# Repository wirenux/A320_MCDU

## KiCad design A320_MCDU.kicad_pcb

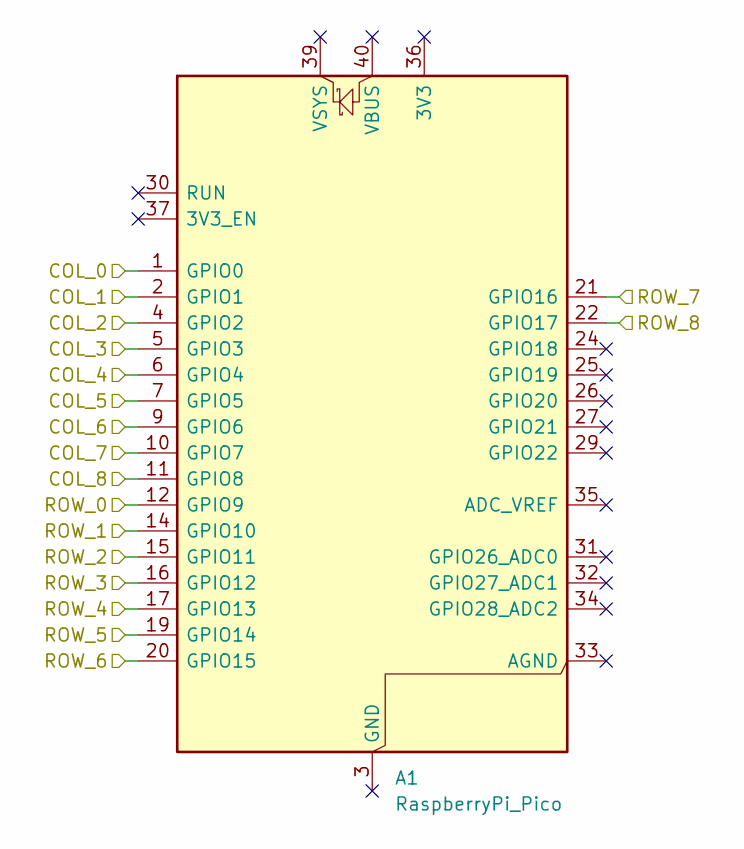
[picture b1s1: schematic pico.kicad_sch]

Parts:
A1: RaspberryPi_Pico; RaspberryPi_Pico_Common_Unspecified

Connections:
/Lower Pad/COL_3: A1.5 (GPIO3); also elsewhere on the board
/Lower Pad/COL_4: A1.6 (GPIO4); also elsewhere on the board
/Lower Pad/COL_5: A1.7 (GPIO5); also elsewhere on the board
/Lower Pad/COL_6: A1.9 (GPIO6); also elsewhere on the board
/Lower Pad/COL_7: A1.10 (GPIO7); also elsewhere on the board
/Lower Pad/ROW_5: A1.19 (GPIO14); also elsewhere on the board
/Lower Pad/ROW_6: A1.20 (GPIO15); also elsewhere on the board
/Lower Pad/ROW_7: A1.21 (GPIO16); also elsewhere on the board
/NumPad/COL_0: A1.1 (GPIO0); also elsewhere on the board
/NumPad/COL_1: A1.2 (GPIO1); also elsewhere on the board
/NumPad/COL_2: A1.4 (GPIO2); also elsewhere on the board
/NumPad/ROW_8: A1.22 (GPIO17); also elsewhere on the board
/Pico/COL_8: A1.11 (GPIO8); also elsewhere on the board
/Pico/ROW_0: A1.12 (GPIO9); also elsewhere on the board
/Pico/ROW_1: A1.14 (GPIO10); also elsewhere on the board
/Pico/ROW_2: A1.15 (GPIO11); also elsewhere on the board
/Pico/ROW_3: A1.16 (GPIO12); also elsewhere on the board
/Pico/ROW_4: A1.17 (GPIO13); also elsewhere on the board

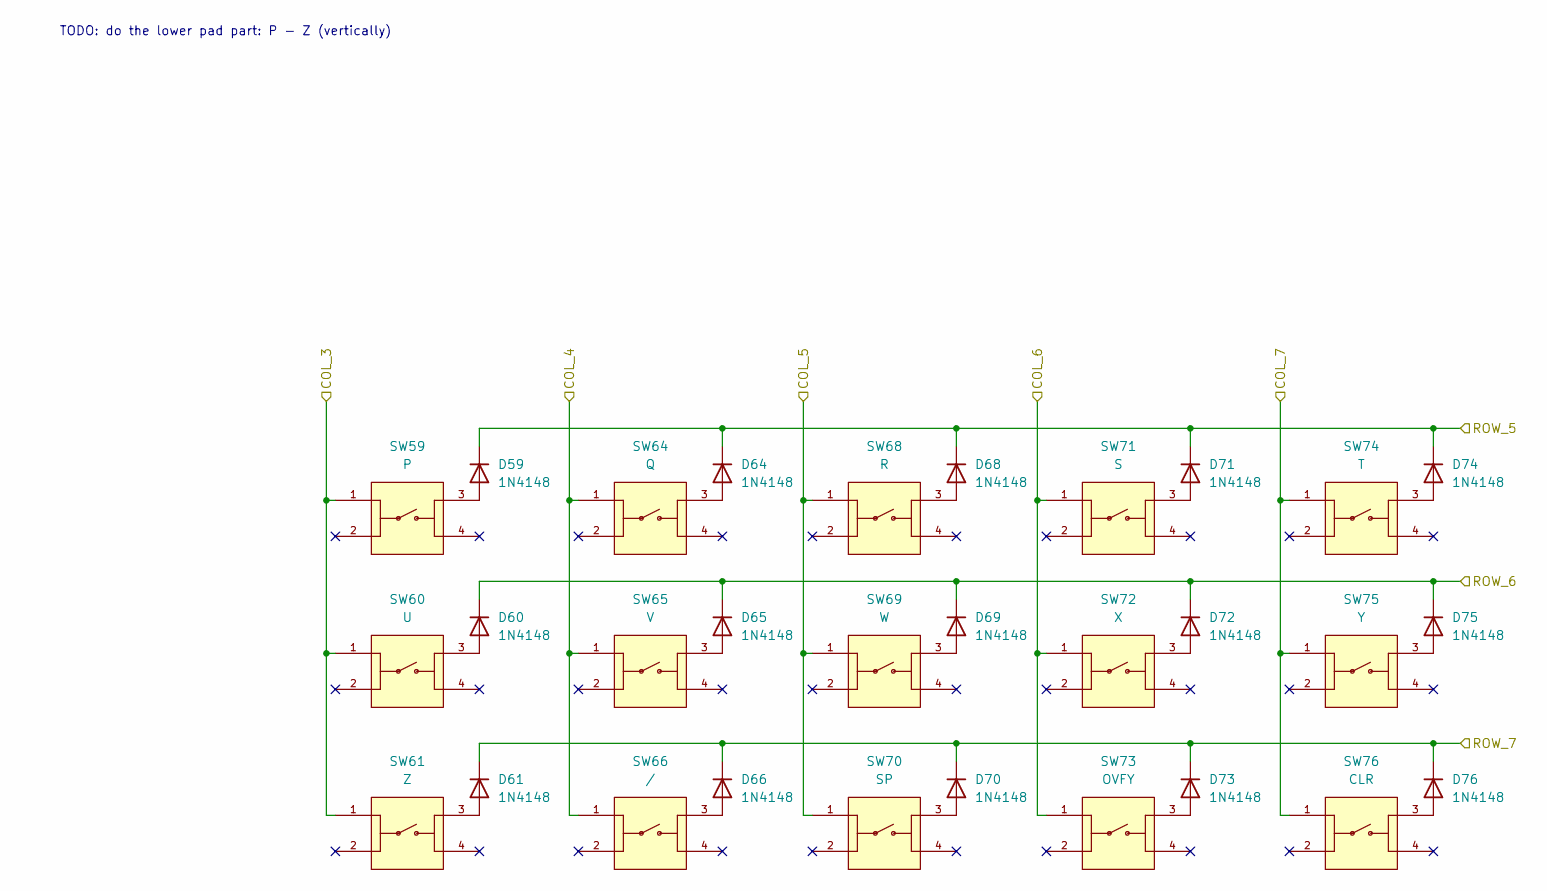
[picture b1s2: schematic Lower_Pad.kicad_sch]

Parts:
D59, D60, D61, D64, D65, D66, D68, D69, D70, D71, D72, D73, D74, D75, D76: 1N4148; D_DO-35_SOD27_P7.62mm_Horizontal
SW59: P; SW_1825910-6-4; PARTREV C10
SW60: U; SW_1825910-6-4; PARTREV C10
SW61: Z; SW_1825910-6-4; PARTREV C10
SW64: Q; SW_1825910-6-4; PARTREV C10
SW65: V; SW_1825910-6-4; PARTREV C10
SW66: /; SW_1825910-6-4; PARTREV C10
SW68: R; SW_1825910-6-4; PARTREV C10
SW69: W; SW_1825910-6-4; PARTREV C10
SW70: SP; SW_1825910-6-4; PARTREV C10
SW71: S; SW_1825910-6-4; PARTREV C10
SW72: X; SW_1825910-6-4; PARTREV C10
SW73: OVFY; SW_1825910-6-4; PARTREV C10
SW74: T; SW_1825910-6-4; PARTREV C10
SW75: Y; SW_1825910-6-4; PARTREV C10
SW76: CLR; SW_1825910-6-4; PARTREV C10

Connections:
/Lower Pad/COL_3: SW59.1, SW60.1, SW61.1; also elsewhere on the board
/Lower Pad/COL_4: SW64.1, SW65.1, SW66.1; also elsewhere on the board
/Lower Pad/COL_5: SW68.1, SW69.1, SW70.1; also elsewhere on the board
/Lower Pad/COL_6: SW71.1, SW72.1, SW73.1; also elsewhere on the board
/Lower Pad/COL_7: SW74.1, SW75.1, SW76.1; also elsewhere on the board
/Lower Pad/ROW_5: D59.1 (K), D64.1 (K), D68.1 (K), D71.1 (K), D74.1 (K); also elsewhere on the board
/Lower Pad/ROW_6: D60.1 (K), D65.1 (K), D69.1 (K), D72.1 (K), D75.1 (K); also elsewhere on the board
/Lower Pad/ROW_7: D61.1 (K), D66.1 (K), D70.1 (K), D73.1 (K), D76.1 (K); also elsewhere on the board
unnamed: D59.2 (A), SW59.3
unnamed: D60.2 (A), SW60.3
unnamed: D61.2 (A), SW61.3
unnamed: D64.2 (A), SW64.3
unnamed: D65.2 (A), SW65.3
unnamed: D66.2 (A), SW66.3
unnamed: D68.2 (A), SW68.3
unnamed: D69.2 (A), SW69.3
unnamed: D70.2 (A), SW70.3
unnamed: D71.2 (A), SW71.3
unnamed: D72.2 (A), SW72.3
unnamed: D73.2 (A), SW73.3
unnamed: D74.2 (A), SW74.3
unnamed: D75.2 (A), SW75.3
unnamed: D76.2 (A), SW76.3

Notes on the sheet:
TODO: do the lower pad part: P - Z (vertically)

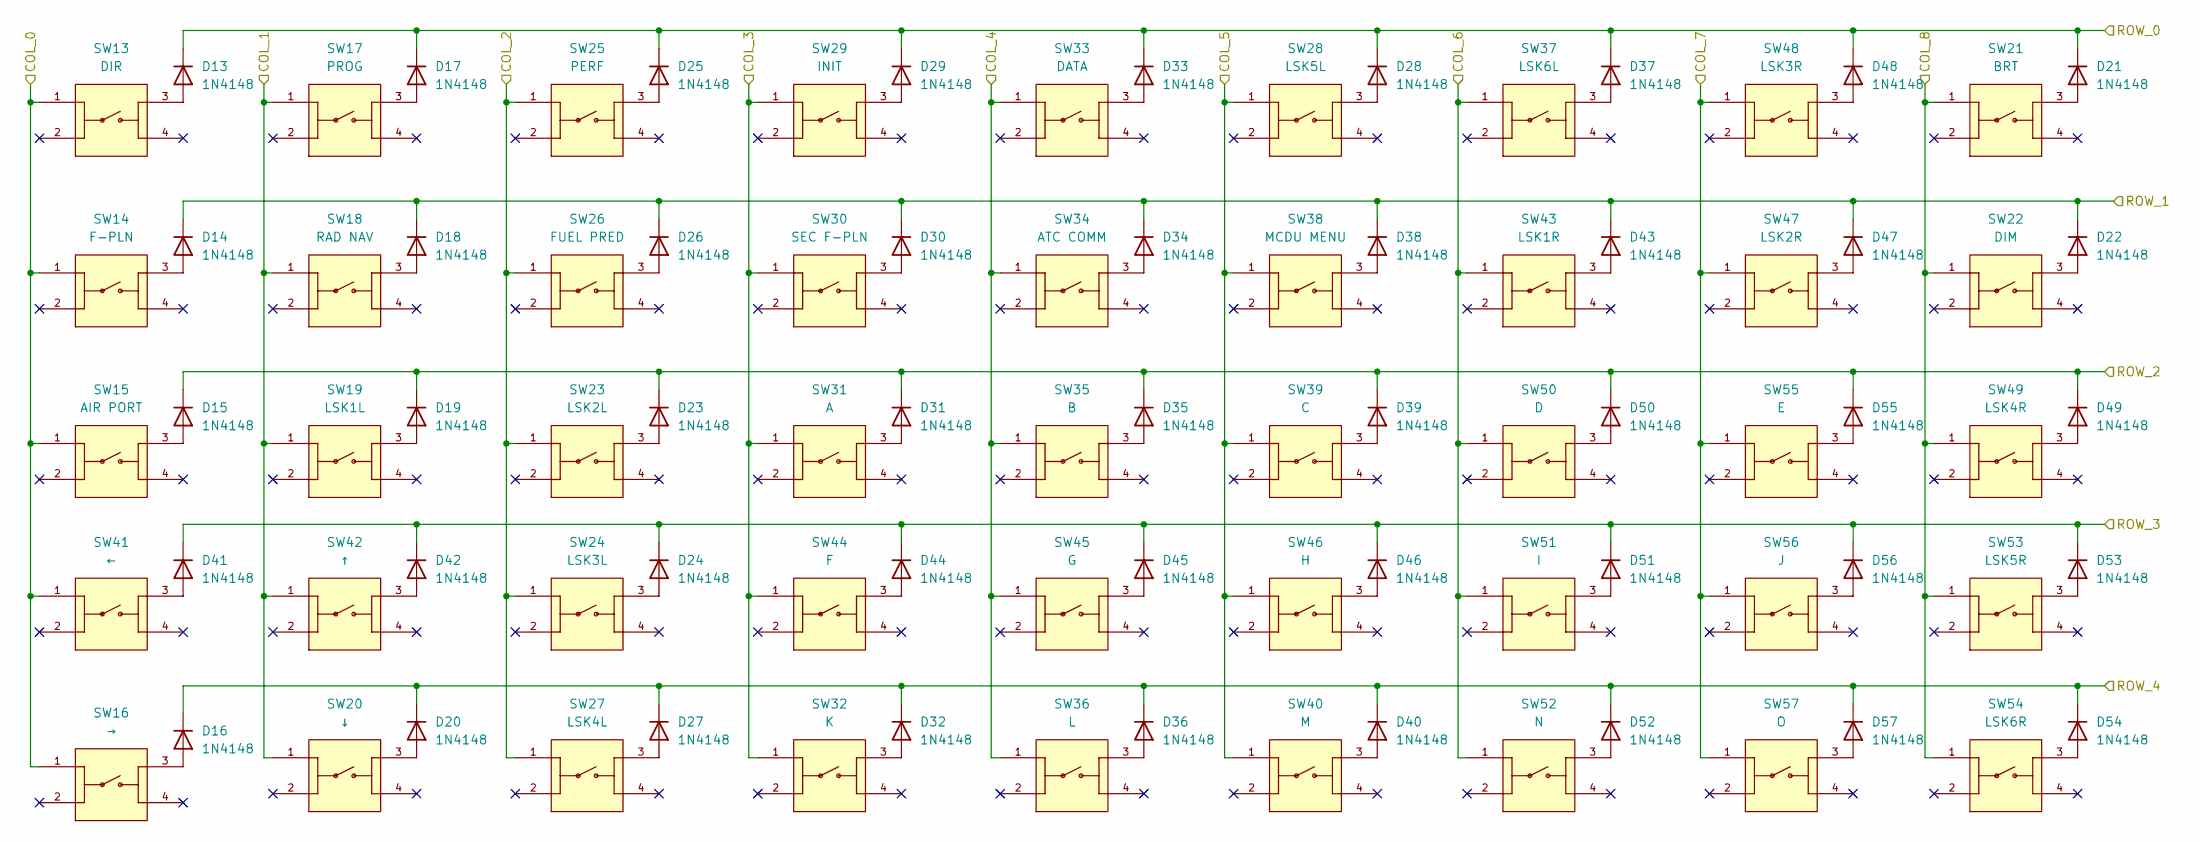
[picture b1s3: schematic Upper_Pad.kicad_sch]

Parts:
D13, D14, D15, D16, D17, D18, D19, D20, D21, D22, D23, D24, D25, D26, D27, D28, D29, D30, D31, D32, D33, D34, D35, D36, D37, D38, D39, D40, D41, D42, D43, D44, D45, D46, D47, D48, D49, D50, D51, D52, D53, D54, D55, D56, D57: 1N4148; D_DO-35_SOD27_P7.62mm_Horizontal
SW13: DIR; SW_1825910-6-4; PARTREV C10
SW14: F-PLN; SW_1825910-6-4; PARTREV C10
SW15: AIR PORT; SW_1825910-6-4; PARTREV C10
SW16: →; SW_1825910-6-4; PARTREV C10
SW17: PROG; SW_1825910-6-4; PARTREV C10
SW18: RAD NAV; SW_1825910-6-4; PARTREV C10
SW19: LSK1L; SW_1825910-6-4; PARTREV C10
SW20: ↓; SW_1825910-6-4; PARTREV C10
SW21: BRT; SW_1825910-6-4; PARTREV C10
SW22: DIM; SW_1825910-6-4; PARTREV C10
SW23: LSK2L; SW_1825910-6-4; PARTREV C10
SW24: LSK3L; SW_1825910-6-4; PARTREV C10
SW25: PERF; SW_1825910-6-4; PARTREV C10
SW26: FUEL PRED; SW_1825910-6-4; PARTREV C10
SW27: LSK4L; SW_1825910-6-4; PARTREV C10
SW28: LSK5L; SW_1825910-6-4; PARTREV C10
SW29: INIT; SW_1825910-6-4; PARTREV C10
SW30: SEC F-PLN; SW_1825910-6-4; PARTREV C10
SW31: A; SW_1825910-6-4; PARTREV C10
SW32: K; SW_1825910-6-4; PARTREV C10
SW33: DATA; SW_1825910-6-4; PARTREV C10
SW34: ATC COMM; SW_1825910-6-4; PARTREV C10
SW35: B; SW_1825910-6-4; PARTREV C10
SW36: L; SW_1825910-6-4; PARTREV C10
SW37: LSK6L; SW_1825910-6-4; PARTREV C10
SW38: MCDU MENU; SW_1825910-6-4; PARTREV C10
SW39: C; SW_1825910-6-4; PARTREV C10
SW40: M; SW_1825910-6-4; PARTREV C10
SW41: ←; SW_1825910-6-4; PARTREV C10
SW42: ↑; SW_1825910-6-4; PARTREV C10
SW43: LSK1R; SW_1825910-6-4; PARTREV C10
SW44: F; SW_1825910-6-4; PARTREV C10
SW45: G; SW_1825910-6-4; PARTREV C10
SW46: H; SW_1825910-6-4; PARTREV C10
SW47: LSK2R; SW_1825910-6-4; PARTREV C10
SW48: LSK3R; SW_1825910-6-4; PARTREV C10
SW49: LSK4R; SW_1825910-6-4; PARTREV C10
SW50: D; SW_1825910-6-4; PARTREV C10
SW51: I; SW_1825910-6-4; PARTREV C10
SW52: N; SW_1825910-6-4; PARTREV C10
SW53: LSK5R; SW_1825910-6-4; PARTREV C10
SW54: LSK6R; SW_1825910-6-4; PARTREV C10
SW55: E; SW_1825910-6-4; PARTREV C10
SW56: J; SW_1825910-6-4; PARTREV C10
SW57: O; SW_1825910-6-4; PARTREV C10

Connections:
/Lower Pad/COL_3: SW29.1, SW30.1, SW31.1, SW32.1, SW44.1; also elsewhere on the board
/Lower Pad/COL_4: SW33.1, SW34.1, SW35.1, SW36.1, SW45.1; also elsewhere on the board
/Lower Pad/COL_5: SW28.1, SW38.1, SW39.1, SW40.1, SW46.1; also elsewhere on the board
/Lower Pad/COL_6: SW37.1, SW43.1, SW50.1, SW51.1, SW52.1; also elsewhere on the board
/Lower Pad/COL_7: SW47.1, SW48.1, SW55.1, SW56.1, SW57.1; also elsewhere on the board
/NumPad/COL_0: SW13.1, SW14.1, SW15.1, SW16.1, SW41.1; also elsewhere on the board
/NumPad/COL_1: SW17.1, SW18.1, SW19.1, SW20.1, SW42.1; also elsewhere on the board
/NumPad/COL_2: SW23.1, SW24.1, SW25.1, SW26.1, SW27.1; also elsewhere on the board
/Pico/COL_8: SW21.1, SW22.1, SW49.1, SW53.1, SW54.1; also elsewhere on the board
/Pico/ROW_0: D13.1 (K), D17.1 (K), D21.1 (K), D25.1 (K), D28.1 (K), D29.1 (K), D33.1 (K), D37.1 (K), D48.1 (K); also elsewhere on the board
/Pico/ROW_1: D14.1 (K), D18.1 (K), D22.1 (K), D26.1 (K), D30.1 (K), D34.1 (K), D38.1 (K), D43.1 (K), D47.1 (K); also elsewhere on the board
/Pico/ROW_2: D15.1 (K), D19.1 (K), D23.1 (K), D31.1 (K), D35.1 (K), D39.1 (K), D49.1 (K), D50.1 (K), D55.1 (K); also elsewhere on the board
/Pico/ROW_3: D24.1 (K), D41.1 (K), D42.1 (K), D44.1 (K), D45.1 (K), D46.1 (K), D51.1 (K), D53.1 (K), D56.1 (K); also elsewhere on the board
/Pico/ROW_4: D16.1 (K), D20.1 (K), D27.1 (K), D32.1 (K), D36.1 (K), D40.1 (K), D52.1 (K), D54.1 (K), D57.1 (K); also elsewhere on the board
unnamed: D13.2 (A), SW13.3
unnamed: D14.2 (A), SW14.3
unnamed: D15.2 (A), SW15.3
unnamed: D16.2 (A), SW16.3
unnamed: D17.2 (A), SW17.3
unnamed: D18.2 (A), SW18.3
unnamed: D19.2 (A), SW19.3
unnamed: D20.2 (A), SW20.3
unnamed: D21.2 (A), SW21.3
unnamed: D22.2 (A), SW22.3
unnamed: D23.2 (A), SW23.3
unnamed: D24.2 (A), SW24.3
unnamed: D25.2 (A), SW25.3
unnamed: D26.2 (A), SW26.3
unnamed: D27.2 (A), SW27.3
unnamed: D28.2 (A), SW28.3
unnamed: D29.2 (A), SW29.3
unnamed: D30.2 (A), SW30.3
unnamed: D31.2 (A), SW31.3
unnamed: D32.2 (A), SW32.3
unnamed: D33.2 (A), SW33.3
unnamed: D34.2 (A), SW34.3
unnamed: D35.2 (A), SW35.3
unnamed: D36.2 (A), SW36.3
unnamed: D37.2 (A), SW37.3
unnamed: D38.2 (A), SW38.3
unnamed: D39.2 (A), SW39.3
unnamed: D40.2 (A), SW40.3
unnamed: D41.2 (A), SW41.3
unnamed: D42.2 (A), SW42.3
unnamed: D43.2 (A), SW43.3
unnamed: D44.2 (A), SW44.3
unnamed: D45.2 (A), SW45.3
unnamed: D46.2 (A), SW46.3
unnamed: D47.2 (A), SW47.3
unnamed: D48.2 (A), SW48.3
unnamed: D49.2 (A), SW49.3
unnamed: D50.2 (A), SW50.3
unnamed: D51.2 (A), SW51.3
unnamed: D52.2 (A), SW52.3
unnamed: D53.2 (A), SW53.3
unnamed: D54.2 (A), SW54.3
unnamed: D55.2 (A), SW55.3
unnamed: D56.2 (A), SW56.3
unnamed: D57.2 (A), SW57.3

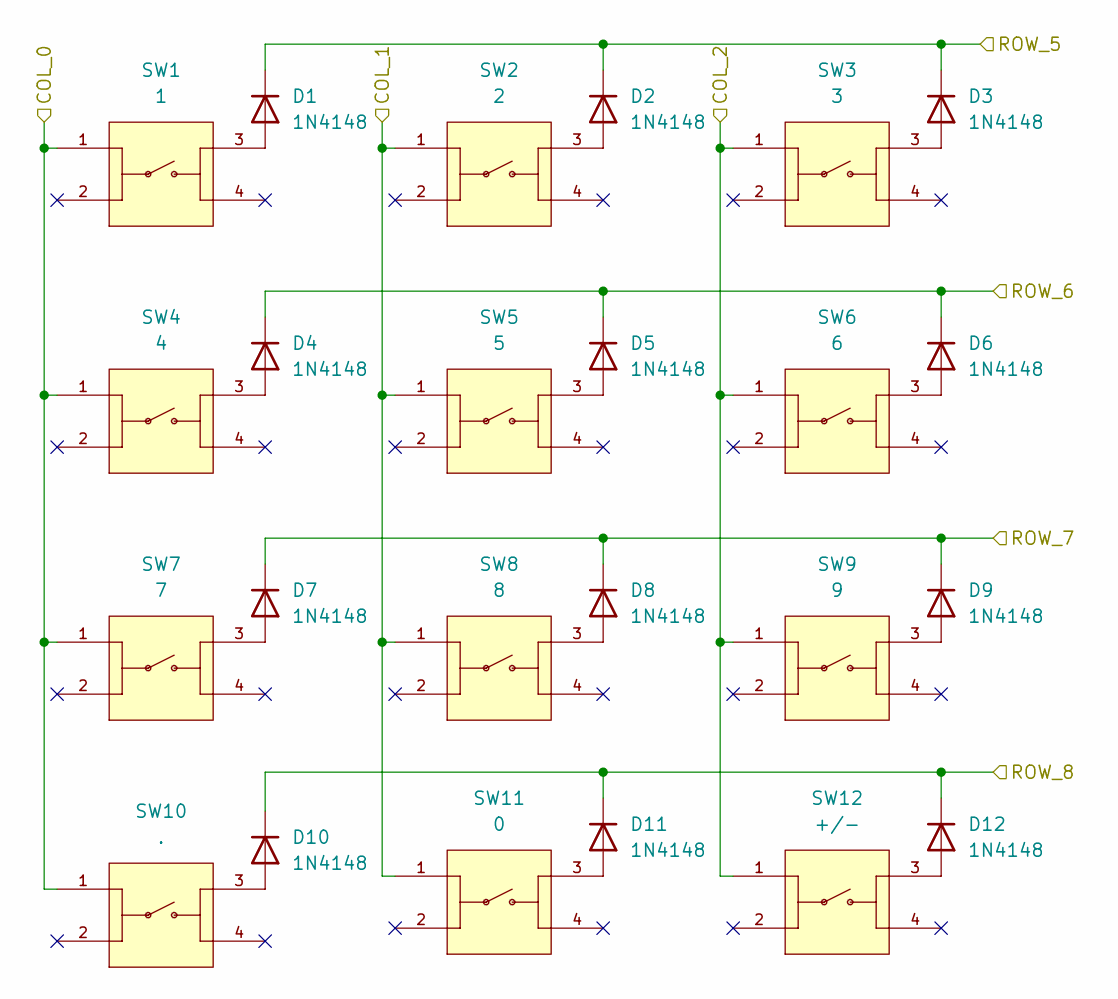
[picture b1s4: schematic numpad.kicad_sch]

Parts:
D1, D2, D3, D4, D5, D6, D7, D8, D9, D10, D11, D12: 1N4148; D_DO-35_SOD27_P7.62mm_Horizontal
SW1: 1; SW_1825910-6-4; PARTREV C10
SW2: 2; SW_1825910-6-4; PARTREV C10
SW3: 3; SW_1825910-6-4; PARTREV C10
SW4: 4; SW_1825910-6-4; PARTREV C10
SW5: 5; SW_1825910-6-4; PARTREV C10
SW6: 6; SW_1825910-6-4; PARTREV C10
SW7: 7; SW_1825910-6-4; PARTREV C10
SW8: 8; SW_1825910-6-4; PARTREV C10
SW9: 9; SW_1825910-6-4; PARTREV C10
SW10: .; SW_1825910-6-4; PARTREV C10
SW11: 0; SW_1825910-6-4; PARTREV C10
SW12: +/-; SW_1825910-6-4; PARTREV C10

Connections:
/Lower Pad/ROW_5: D1.1 (K), D2.1 (K), D3.1 (K); also elsewhere on the board
/Lower Pad/ROW_6: D4.1 (K), D5.1 (K), D6.1 (K); also elsewhere on the board
/Lower Pad/ROW_7: D7.1 (K), D8.1 (K), D9.1 (K); also elsewhere on the board
/NumPad/COL_0: SW1.1, SW4.1, SW7.1, SW10.1; also elsewhere on the board
/NumPad/COL_1: SW2.1, SW5.1, SW8.1, SW11.1; also elsewhere on the board
/NumPad/COL_2: SW3.1, SW6.1, SW9.1, SW12.1; also elsewhere on the board
/NumPad/ROW_8: D10.1 (K), D11.1 (K), D12.1 (K); also elsewhere on the board
unnamed: D1.2 (A), SW1.3
unnamed: D2.2 (A), SW2.3
unnamed: D3.2 (A), SW3.3
unnamed: D4.2 (A), SW4.3
unnamed: D5.2 (A), SW5.3
unnamed: D6.2 (A), SW6.3
unnamed: D7.2 (A), SW7.3
unnamed: D8.2 (A), SW8.3
unnamed: D9.2 (A), SW9.3
unnamed: D10.2 (A), SW10.3
unnamed: D11.2 (A), SW11.3
unnamed: D12.2 (A), SW12.3

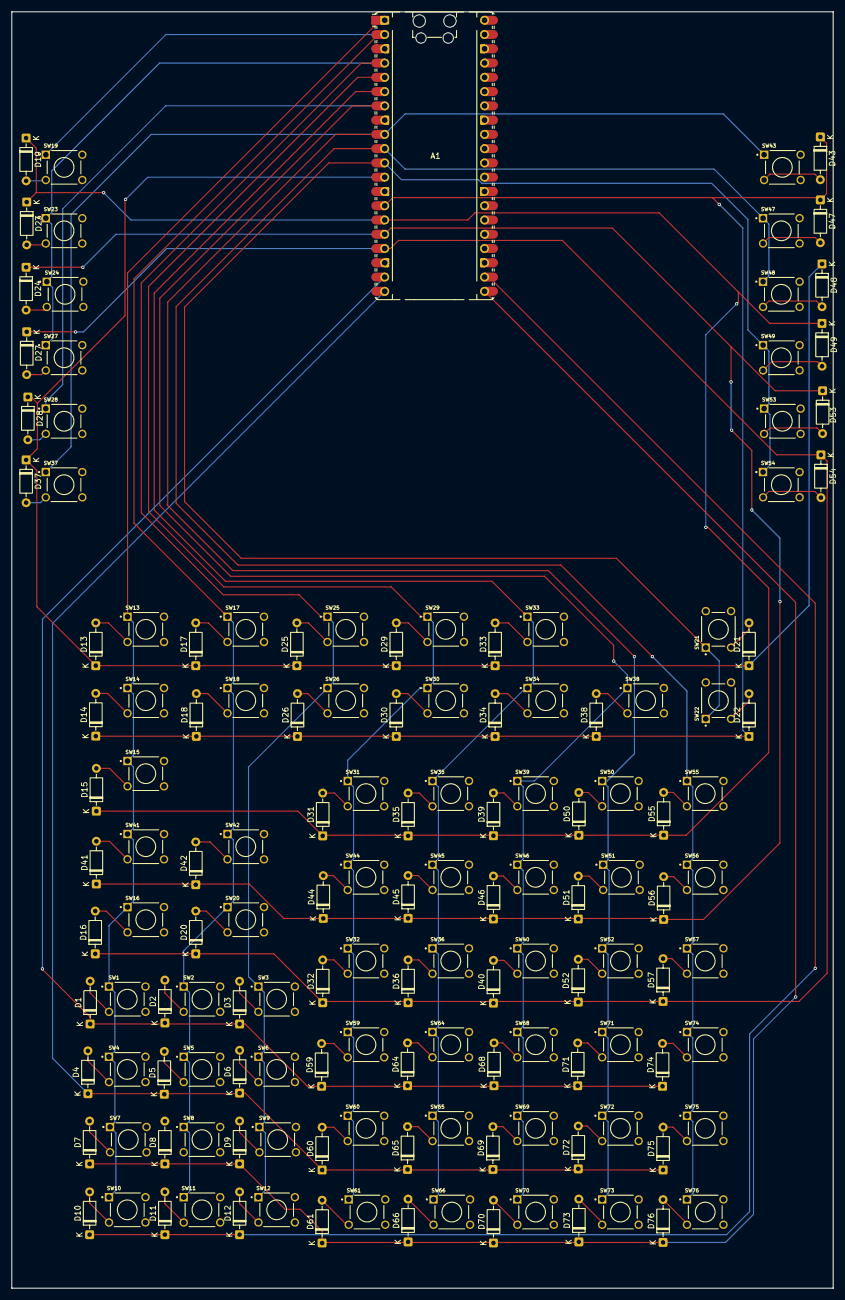
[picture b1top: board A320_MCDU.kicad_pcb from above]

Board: 2 copper layers, 146.2 x 227.2 mm, 145 parts (0 on the bottom side), 90 nets.

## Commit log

2026-06-04 update: .gitignore
2026-06-04 Finished all button
2026-06-04 add: TODO
2026-06-05 Add: PCB Part, NumPad Mesurement
2026-06-05 Add: PCB Part, Just need routage rn
2026-06-05 Finished: PCB
2026-06-05 add: screenshot
